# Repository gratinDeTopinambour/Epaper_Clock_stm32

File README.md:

# Epaper_Clock_display

A silent, light-free bedside clock built with:

- **STM32F103C** (“Blue Pill”)
- **ESP-01** (Wi‑Fi)
- **3.52" e-paper HAT (B)**
- **BME280** (temperature, humidity, pressure sensor)

No display backlight, no ticking noise – ideal to keep next to your bed without disturbing sleep.

---

## Features

- **Always-readable e-paper display**
  - Time and date
  - Temperature, humidity (BME280)
- **Low light pollution**
  - E-paper only refreshes when needed
  - No LEDs or backlight by default
- **Wi‑Fi connectivity (ESP‑01)**
  - Intended for time sync
---

## Project Structure

```text
Epaper_Clock_stm32/
├─ 3D_print/                 # Enclosure and mechanical parts
├─ Electronics and schematics/  # Schematics, PCB files, wiring diagrams
└─ Stm32 Code/               # STM32 firmware (CubeIDE project)
```

- **`3D_print/`**  
  Contains all files related to the case/enclosure:
  - STL files for 3D printing

- **`Electronics and schematics/`**  
  Contains all electronics documentation:
  - Schematics
  - gerber

- **`Stm32 Code/`**  
  STM32CubeIDE project implementing:
  - Display update logic
  - Sensor reading (BME280 via I2C)
  - Interface with ESP‑01 (UART)
  - Timer-based refresh (TIM3, 1‑minute interrupt)  
---

## Hardware Overview

- **MCU**: STM32F103C
- **Display**: 3.52" e-paper HAT (B)
- **Wi‑Fi module**: ESP‑01
- **Sensor**: BME280
- **Power**: 5 V input (e.g. USB), with on-board regulation to 3.3 V for logic

---

## Getting Started

1. **Print the enclosure**  
   - Open `3D_print/` and print the parts

2. **Build the electronics**  
   - Use the schematics and wiring diagrams from `Electronics and schematics/`.

3. **Flash the STM32 firmware**
   - Open the project in **STM32CubeIDE** from the `Stm32 Code/` folder.
   - Check that the pin configuration matches your STM32 variant and board.
   - Build and flash using an ST‑Link.

4. **Assemble the clock**
   - Mount the boards and e‑paper into the printed enclosure.
   - Route cables and ensure no strain on connectors.
   - Close the enclosure.

---

## Future Improvements / Ideas

- Meteo information
- Battery backup

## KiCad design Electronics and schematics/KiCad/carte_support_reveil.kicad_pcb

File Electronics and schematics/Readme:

folder with all electronics part

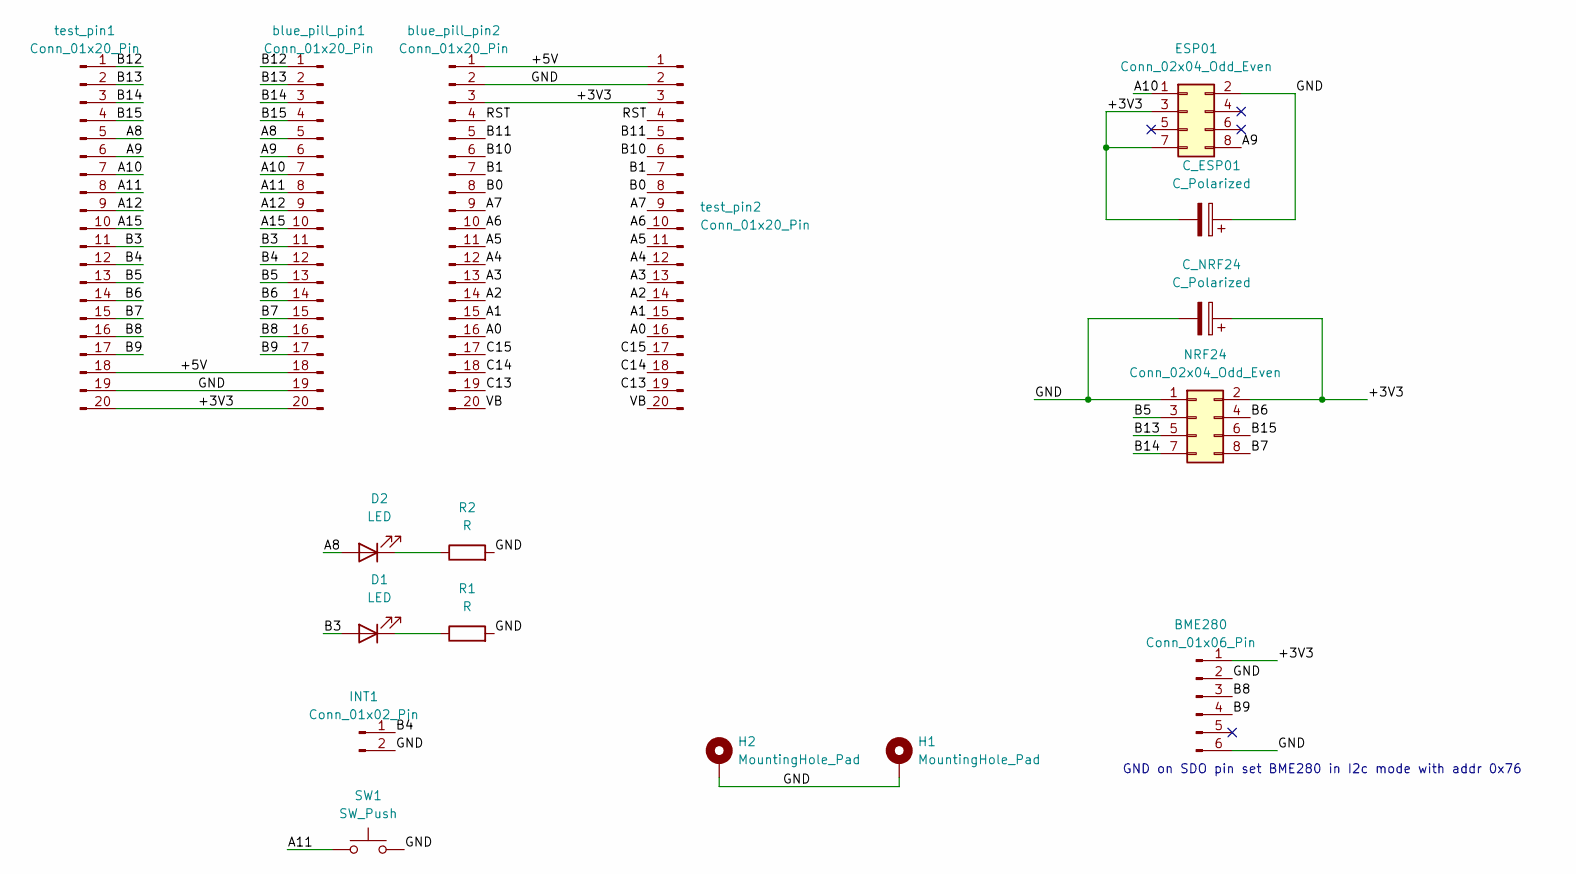
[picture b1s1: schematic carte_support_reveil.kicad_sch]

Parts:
BME280: Conn_01x06_Pin; PinHeader_1x06_P2.54mm_Vertical
C_ESP01: C_Polarized; C_Radial_D6.3mm_H11.0mm_P2.50mm
C_NRF24: C_Polarized; C_Radial_D6.3mm_H11.0mm_P2.50mm
D1, D2: LED; LED_D5.0mm
ESP01: Conn_02x04_Odd_Even; PinHeader_2x04_P2.54mm_Vertical
H1, H2: MountingHole_Pad; MountingHole_3.2mm_M3_Pad_Via
INT1: Conn_01x02_Pin; PinHeader_1x02_P2.54mm_Vertical
NRF24: Conn_02x04_Odd_Even; PinHeader_2x04_P2.54mm_Vertical
R1, R2: R; R_Axial_DIN0411_L9.9mm_D3.6mm_P15.24mm_Horizontal
SW1: SW_Push; SW_PUSH_6mm_H5mm
blue_pill_pin1, blue_pill_pin2: Conn_01x20_Pin; PinHeader_1x20_P2.54mm_Vertical
test_pin1, test_pin2: Conn_01x20_Pin; PinHeader_1x20_P2.54mm_Vertical

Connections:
/+3V3: BME280.1, C_ESP01.2, C_NRF24.1, ESP01.3, ESP01.7, NRF24.2, blue_pill_pin1.20, blue_pill_pin2.3, test_pin1.20, test_pin2.3
/+5V: blue_pill_pin1.18, blue_pill_pin2.1, test_pin1.18, test_pin2.1
/A0: blue_pill_pin2.16, test_pin2.16
/A1: blue_pill_pin2.15, test_pin2.15
/A2: blue_pill_pin2.14, test_pin2.14
/A3: blue_pill_pin2.13, test_pin2.13
/A4: blue_pill_pin2.12, test_pin2.12
/A5: blue_pill_pin2.11, test_pin2.11
/A6: blue_pill_pin2.10, test_pin2.10
/A7: blue_pill_pin2.9, test_pin2.9
/A8: D2.2 (A), blue_pill_pin1.5, test_pin1.5
/A9: ESP01.8, blue_pill_pin1.6, test_pin1.6
/A10: ESP01.1, blue_pill_pin1.7, test_pin1.7
/A11: SW1.1, blue_pill_pin1.8, test_pin1.8
/A12: blue_pill_pin1.9, test_pin1.9
/A15: blue_pill_pin1.10, test_pin1.10
/B0: blue_pill_pin2.8, test_pin2.8
/B1: blue_pill_pin2.7, test_pin2.7
/B3: D1.2 (A), blue_pill_pin1.11, test_pin1.11
/B4: INT1.1, blue_pill_pin1.12, test_pin1.12
/B5: NRF24.3, blue_pill_pin1.13, test_pin1.13
/B6: NRF24.4, blue_pill_pin1.14, test_pin1.14
/B7: NRF24.8, blue_pill_pin1.15, test_pin1.15
/B8: BME280.3, blue_pill_pin1.16, test_pin1.16
/B9: BME280.4, blue_pill_pin1.17, test_pin1.17
/B10: blue_pill_pin2.6, test_pin2.6
/B11: blue_pill_pin2.5, test_pin2.5
/B12: blue_pill_pin1.1, test_pin1.1
/B13: NRF24.5, blue_pill_pin1.2, test_pin1.2
/B14: NRF24.7, blue_pill_pin1.3, test_pin1.3
/B15: NRF24.6, blue_pill_pin1.4, test_pin1.4
/C13: blue_pill_pin2.19, test_pin2.19
/C14: blue_pill_pin2.18, test_pin2.18
/C15: blue_pill_pin2.17, test_pin2.17
/GND: BME280.2, BME280.6, C_ESP01.1, C_NRF24.2, ESP01.2, H1.1, H2.1, INT1.2, NRF24.1, R1.2, R2.2, SW1.2, blue_pill_pin1.19, blue_pill_pin2.2, test_pin1.19, test_pin2.2
/RST: blue_pill_pin2.4, test_pin2.4
/VB: blue_pill_pin2.20, test_pin2.20
unnamed: D1.1 (K), R1.1
unnamed: D2.1 (K), R2.1

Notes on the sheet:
GND on SDO pin set BME280 in I2c mode with addr 0x76

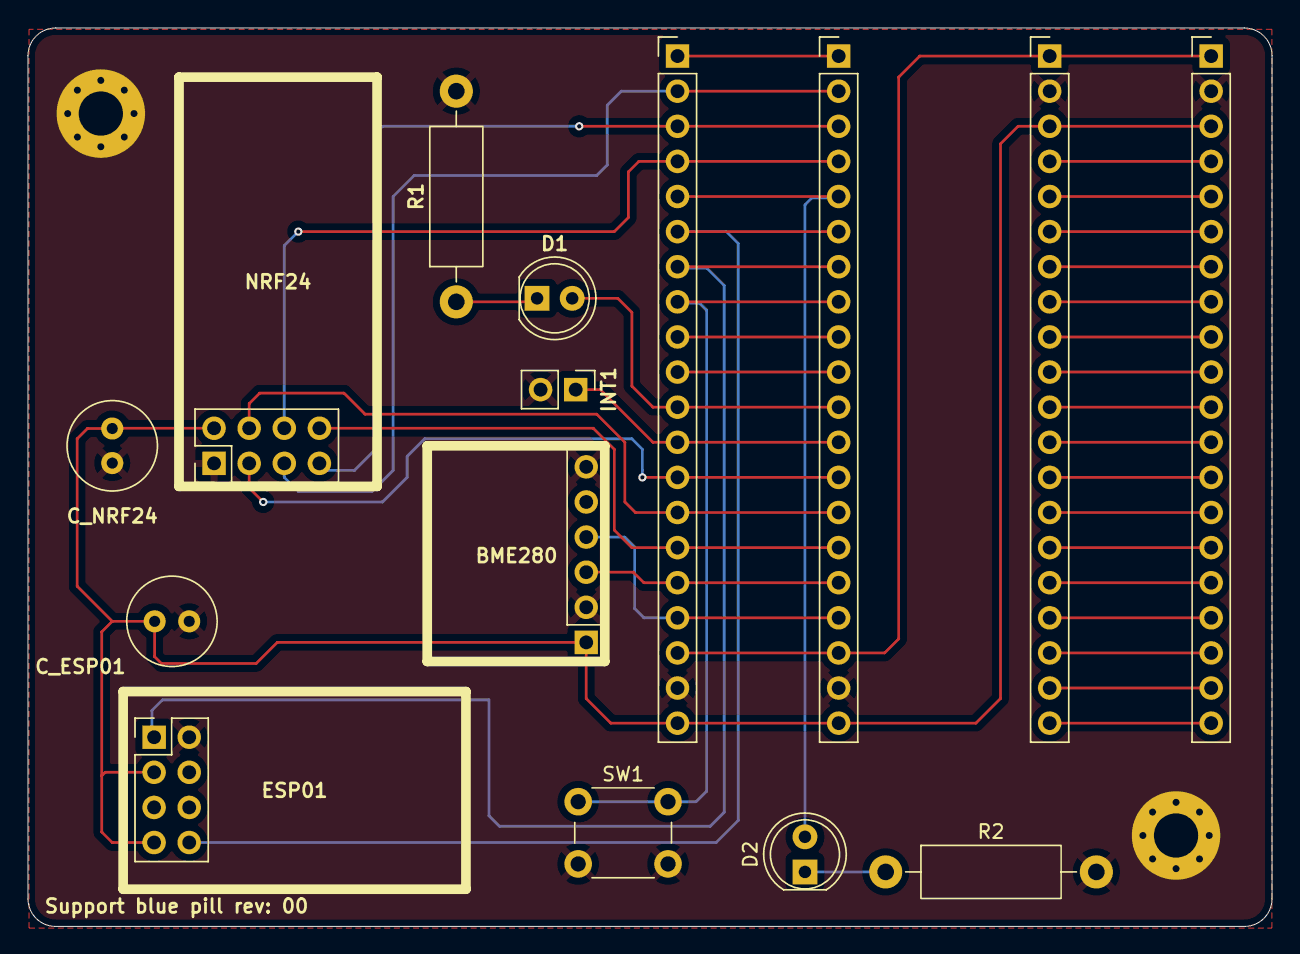
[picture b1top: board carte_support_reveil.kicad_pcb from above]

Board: 2 copper layers, 90.0 x 65.0 mm, 17 parts (0 on the bottom side), 39 nets.

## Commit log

2026-01-15 Create electronic directory
2026-01-15 Create setup
2026-01-19 Rename .setting/com.st.stm32cube.ide.mcu.sfrview.prefs to STM 32/NUCLEO_STM32F072RB/.setting/com.st.stm32cube.ide.mcu.sfrview.prefs
2026-01-19 Rename com.st.stm32cube.ide.mcu.sfrview.prefs to com.st.stm32cube.ide.mcu.sfrview.prefs
2026-01-24 Rename Stm32 Code/NUCLEO_STM32F072RB/STM32F103CB/STM32F103CBTX_FLASH.ld to Stm32 Code/STM32F103CB/STM32F103CBTX_FLASH.ld
